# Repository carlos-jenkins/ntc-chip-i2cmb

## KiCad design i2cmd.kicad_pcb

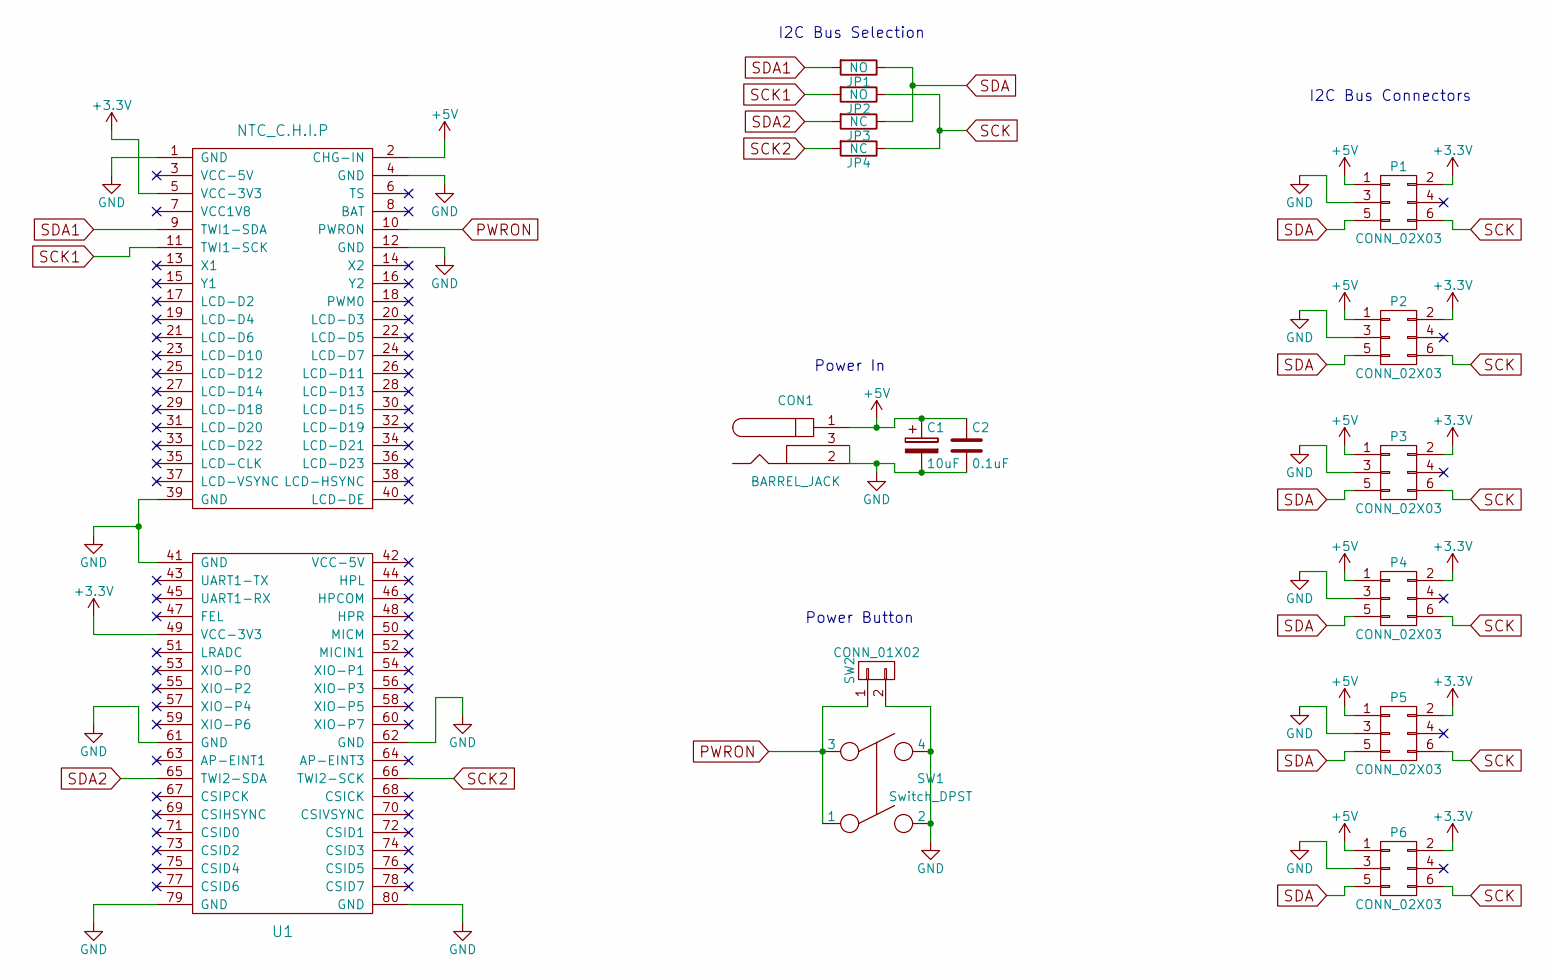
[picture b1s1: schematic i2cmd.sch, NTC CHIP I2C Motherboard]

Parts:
C1: 10uF; C_Radial_D5_L6_P2.5
C2: 0.1uF; C_Disc_D3_P2.5
CON1: BARREL_JACK
JP1, JP2: NO; R_0201
JP3, JP4: NC; R_0201
P1, P2, P3, P4, P5, P6: CONN_02X03; Pin_Header_Straight_2x03
SW1: Switch_DPST; sw_push_small
SW2: CONN_01X02; Pin_Header_Straight_1x02
U1: NTC_C.H.I.P; ntc_chip

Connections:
+3V3: P1.2, P2.2, P3.2, P4.2, P5.2, P6.2, U1.5 (VCC-3V3), U1.49 (VCC-3V3)
+5V: C1.1, C2.1, CON1.1, P1.1, P2.1, P3.1, P4.1, P5.1, P6.1, U1.2 (CHG-IN)
GND: C1.2, C2.2, CON1.2, CON1.3, P1.3, P2.3, P3.3, P4.3, P5.3, P6.3, SW1.2, SW1.4, SW2.2, U1.1 (GND), U1.4 (GND), U1.12 (GND), U1.39 (GND), U1.41 (GND), U1.61 (GND), U1.62 (GND), U1.79 (GND), U1.80 (GND)
PWRON: SW1.1, SW1.3, SW2.1, U1.10 (PWRON)
SCK: JP2.1, JP4.1, P1.6, P2.6, P3.6, P4.6, P5.6, P6.6
SCK1: JP2.2, U1.11 (TWI1-SCK)
SCK2: JP4.2, U1.66 (TWI2-SCK)
SDA: JP1.1, JP3.1, P1.5, P2.5, P3.5, P4.5, P5.5, P6.5
SDA1: JP1.2, U1.9 (TWI1-SDA)
SDA2: JP3.2, U1.65 (TWI2-SDA)

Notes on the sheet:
I2C Bus Selection
Power In
I2C Bus Connectors
Power Button

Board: 2 copper layers, 16 parts (0 on the bottom side), 10 nets, no tracks yet.

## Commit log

2016-08-12 Initial version of the schematic.
2016-08-12 Added netlist and base footprints.
2016-08-12 Added initial version of the board.
2016-08-12 Improvements on the silkscreen.
